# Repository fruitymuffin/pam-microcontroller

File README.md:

# pam-microcontroller
The AVR controller is based on the AVR64DA32 chip which is programmed via the UPDI interface.

## 1. Compiling
The C/C++ code is compiled using avr-gcc/avr-g++ and makes use of avr-libc. [Microchip Studio](https://www.microchip.com/en-us/tools-resources/develop/microchip-studio) was used as the IDE as it integrates the avr-g++ toolchain so building is easy.

## 2. Uploading
The serialUPDI interface was used to upload .hex or .elf files to the chip with the help of [avrdude](https://github.com/avrdudes/avrdude). An avrdude upload command can be added to Microchip Studio as a external tool to make uploading executables easier.
Go to Tools->External Tools and add a new tool. The tool was configured as:

Command:
```
C:\Program Files\avrdude-v7.3-windows-x64\avrdude.exe
```
Arguments:
```
-p avr64da32 -P COM5 -b 115200 -c serialupdi -C "C:\Program Files\avrdude-v7.3-windows-x64\avrdude.conf" -U flash:w:$(BinDir)\led-controller.hex:i
```

Initial Directory:
```
$(BinDir)
```

In order to set fuses with avrdude on the newer DA series chips, it was necessary to manually write it. Luckily the corrent fuse locations are specified in avrdude.conf under the DX family information. To enable the reset pin, the fuse was written by:
```
avrdude -c serialupdi -p avr64da32 -P com5 -U syscfg0:w:0xC8:m
```

## 3. Serial communication
The avr controller has a FTDI 230XS usb to serial chip. Which will typically show up as /dev/ttyUSBn on linux. To write to the port, we can open it as a file using fopen, however to do so we need to know which tty port our device is on. The device is not guaranteed to always be /dev/ttyUSB0.
To be able to access it consistently we can create a symlink to a known filename by creating a udev rule.

Create a file caled "N-my-rule.rules" in ```/etc/udev/rules.d/``` with the contents:
```
SUBSYSTEM=="tty", ATTRS{idVendor}=="0403", ATTRS{idProduct}=="6015", ATTRS{serial}=="DU0D13LG", SYMLINK+="ttypam-serial"
```

This creates a symlink called ```ttypam-serial``` to the tty port which matches the properties given (idVendor, idProduct, serial), so that we can now use ```/dev/ttypam-serial``` to access our device.

To get the required USB device info use:
```
udevadm info -a -n /dev/ttyUSB0 | grep '{serial}\|{idProduct}\|{idVendor}' | head -n3
```
Where ttyUSB0 is replaced with the tty port of the device. See ```lsusb```.

It might also be necessary to add the user to the dialout group to get permissions to usb devices.

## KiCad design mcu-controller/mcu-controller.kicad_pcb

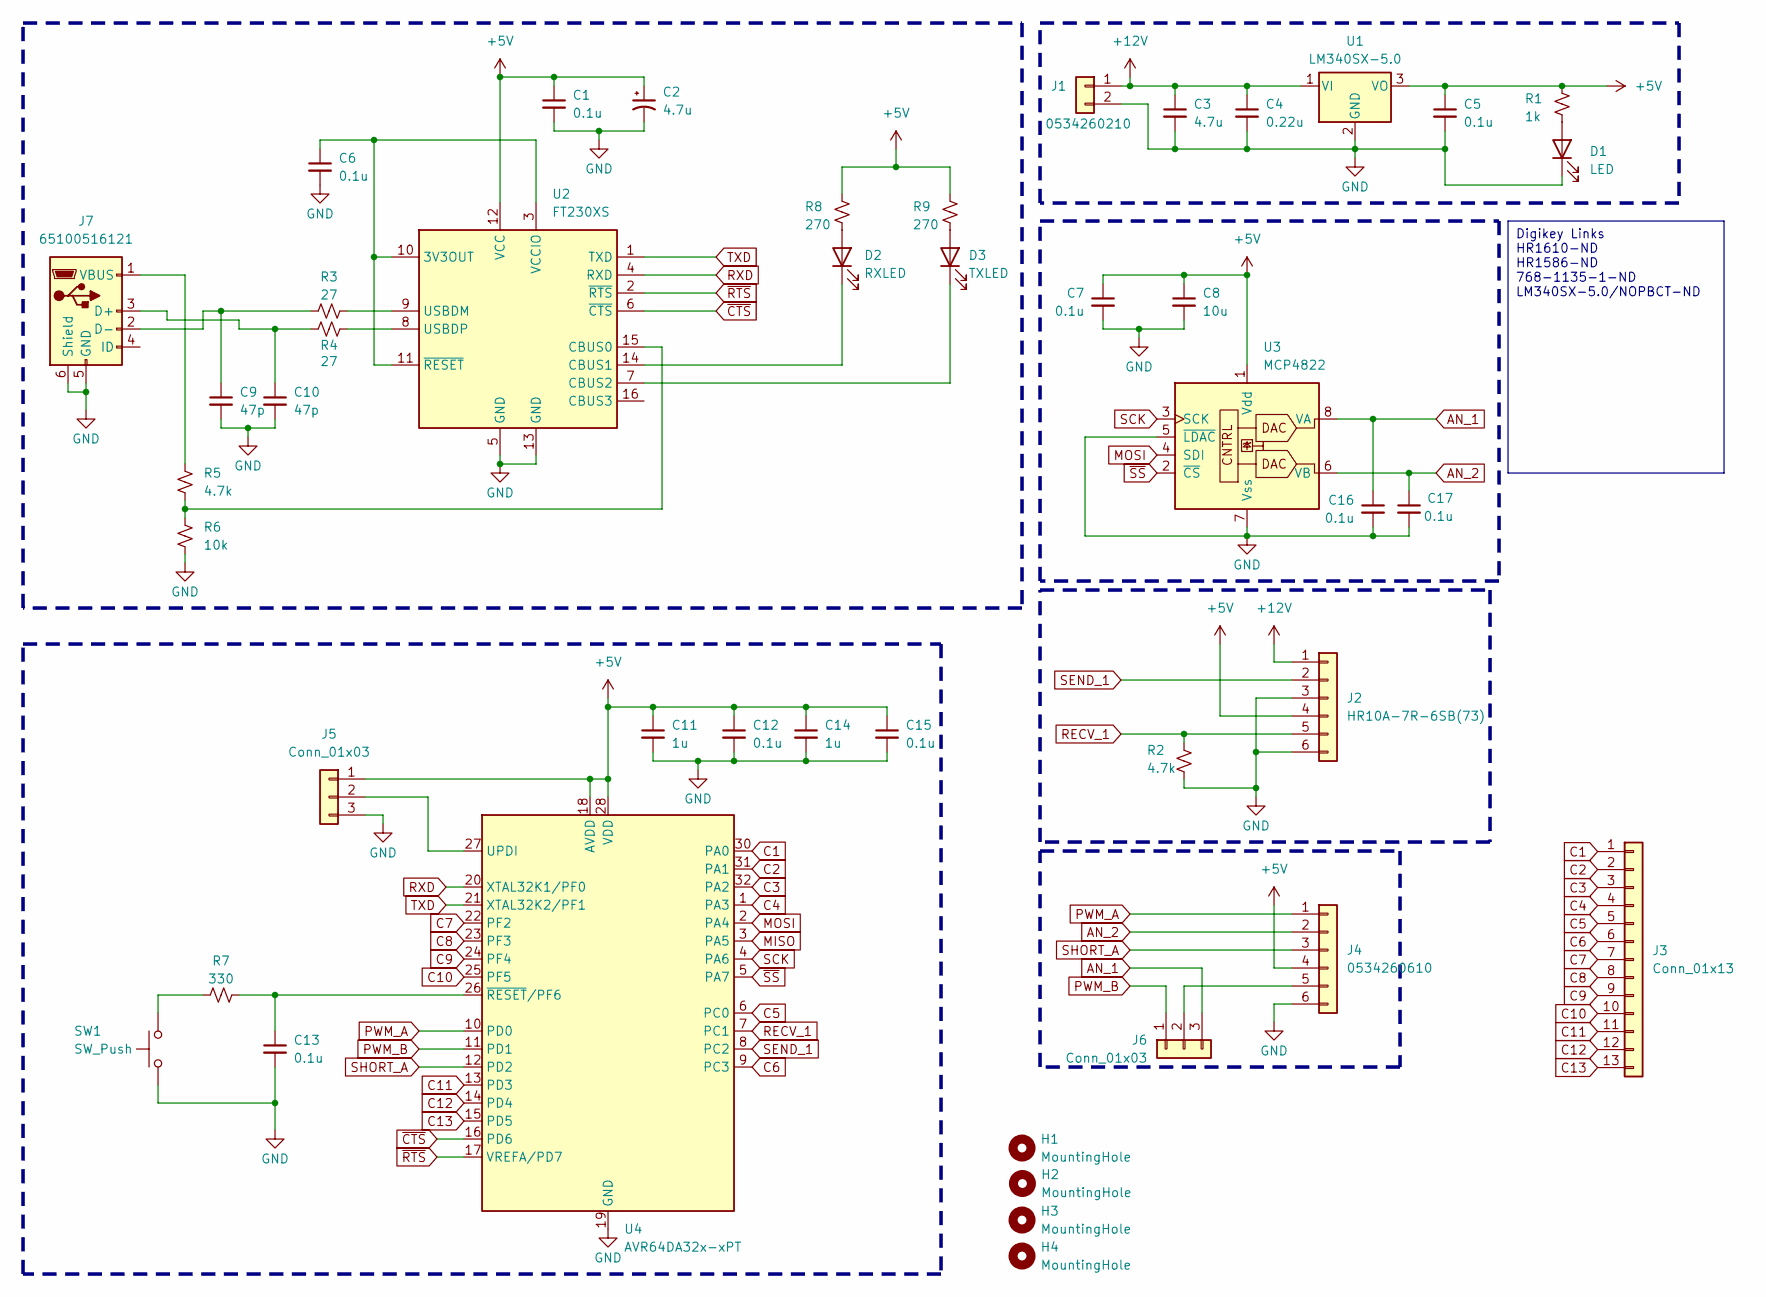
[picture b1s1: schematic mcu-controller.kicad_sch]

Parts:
C1, C5, C6, C7, C12, C13, C15, C16, C17: 0.1u; C_0805_2012Metric
C2, C3: 4.7u; C_0805_2012Metric
C4: 0.22u; C_0805_2012Metric
C8: 10u; C_1206_3216Metric
C9, C10: 47p; C_0805_2012Metric
C11, C14: 1u; C_0805_2012Metric
D1: LED; LED_0805_2012Metric
D2: RXLED; LED_0805_2012Metric
D3: TXLED; LED_0805_2012Metric
H1, H2, H3, H4: MountingHole; MountingHole_3.2mm_M3
J1: 0534260210; CON_534260210_MOL
J2: HR10A-7R-6SB(73)
J3: Conn_01x13; PinHeader_1x13_P2.54mm_Vertical
J4: 0534260610; CON_534260610_MOL
J5, J6: Conn_01x03; PinHeader_1x03_P2.54mm_Vertical
J7: 65100516121; USB_Mini-B_Wuerth_65100516121_Horizontal
R1: 1k; R_0805_2012Metric
R2, R5: 4.7k; R_0805_2012Metric
R3, R4: 27; R_0805_2012Metric
R6: 10k; R_0805_2012Metric
R7: 330; R_0805_2012Metric
R8, R9: 270; R_0805_2012Metric
SW1: SW_Push; SW_SPST_FSMSM
U1: LM340SX-5.0; TO-263-3_TabPin2
U2: FT230XS; SSOP-16_3.9x4.9mm_P0.635mm
U3: MCP4822; SOIC-8_3.9x4.9mm_P1.27mm
U4: AVR64DA32x-xPT; TQFP-32_7x7mm_P0.8mm

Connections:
+5V: C1.1, C2.1, C5.1, C7.1, C8.1, C11.1, C12.1, C14.1, C15.1, J2.4, J4.4, J5.1, R1.1, R8.1, R9.1, U1.3 (VO), U2.12 (VCC), U3.1 (Vdd), U4.18 (AVDD), U4.28 (VDD)
+12V: C3.1, C4.1, J1.1, J2.1, U1.1 (VI)
AN_1: C16.1, J6.3, U3.8 (VA)
AN_2: C17.1, J4.2, U3.6 (VB)
C1: J3.1, U4.30 (PA0)
C2: J3.2, U4.31 (PA1)
C3: J3.3, U4.32 (PA2)
C4: J3.4, U4.1 (PA3)
C5: J3.5, U4.6 (PC0)
C6: J3.6, U4.9 (PC3)
C7: J3.7, U4.22 (PF2)
C8: J3.8, U4.23 (PF3)
C9: J3.9, U4.24 (PF4)
C10: J3.10, U4.25 (PF5)
C11: J3.11, U4.13 (PD3)
C12: J3.12, U4.14 (PD4)
C13: J3.13, U4.15 (PD5)
GND: C1.2, C2.2, C3.2, C4.2, C5.2, C6.2, C7.2, C8.2, C9.2, C10.2, C11.2, C12.2, C13.2, C14.2, C15.2, C16.2, C17.2, D1.1 (K), J1.2, J2.3, J2.6, J4.6, J5.3, J7.5 (GND), J7.6 (Shield), R2.2, R6.2, SW1.1, U1.2 (GND), U2.5 (GND), U2.13 (GND), U3.5 (~LDAC), U3.7 (Vss), U4.19 (GND), U4.29 (GND)
MISO: U4.3 (PA5)
MOSI: U3.4 (SDI), U4.2 (PA4)
unnamed: D1.2 (A), R1.2
unnamed: D2.2 (A), R8.2
unnamed: D2.1 (K), U2.14 (CBUS1)
unnamed: D3.2 (A), R9.2
unnamed: D3.1 (K), U2.7 (CBUS2)
unnamed: J4.5, J6.2
unnamed: J5.2, U4.27 (UPDI)
unnamed: C10.1, J7.3 (D+), R4.1
unnamed: C9.1, J7.2 (D-), R3.1
unnamed: J7.1 (VBUS), R5.1
unnamed: R7.1, SW1.2
unnamed: C6.1, U2.3 (VCCIO), U2.10 (3V3OUT), U2.11 (~RESET)
unnamed: R5.2, R6.1, U2.15 (CBUS0)
unnamed: R3.2, U2.9 (USBDM)
unnamed: R4.2, U2.8 (USBDP)
unnamed: C13.1, R7.2, U4.26 (~RESET/PF6)
PWM_A: J4.1, U4.10 (PD0)
PWM_B: J6.1, U4.11 (PD1)
RECV_1: J2.5, R2.1, U4.7 (PC1)
RXD: U2.4 (RXD), U4.20 (XTAL32K1/PF0)
SCK: U3.3 (SCK), U4.4 (PA6)
SEND_1: J2.2, U4.8 (PC2)
SHORT_A: J4.3, U4.12 (PD2)
TXD: U2.1 (TXD), U4.21 (XTAL32K2/PF1)
~CTS: U2.6 (~CTS), U4.16 (PD6)
~RTS: U2.2 (~RTS), U4.17 (VREFA/PD7)
~SS: U3.2 (~CS), U4.5 (PA7)

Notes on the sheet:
Digikey Links HR1610-ND HR1586-ND 768-1135-1-ND LM340SX-5.0/NOPBCT-ND

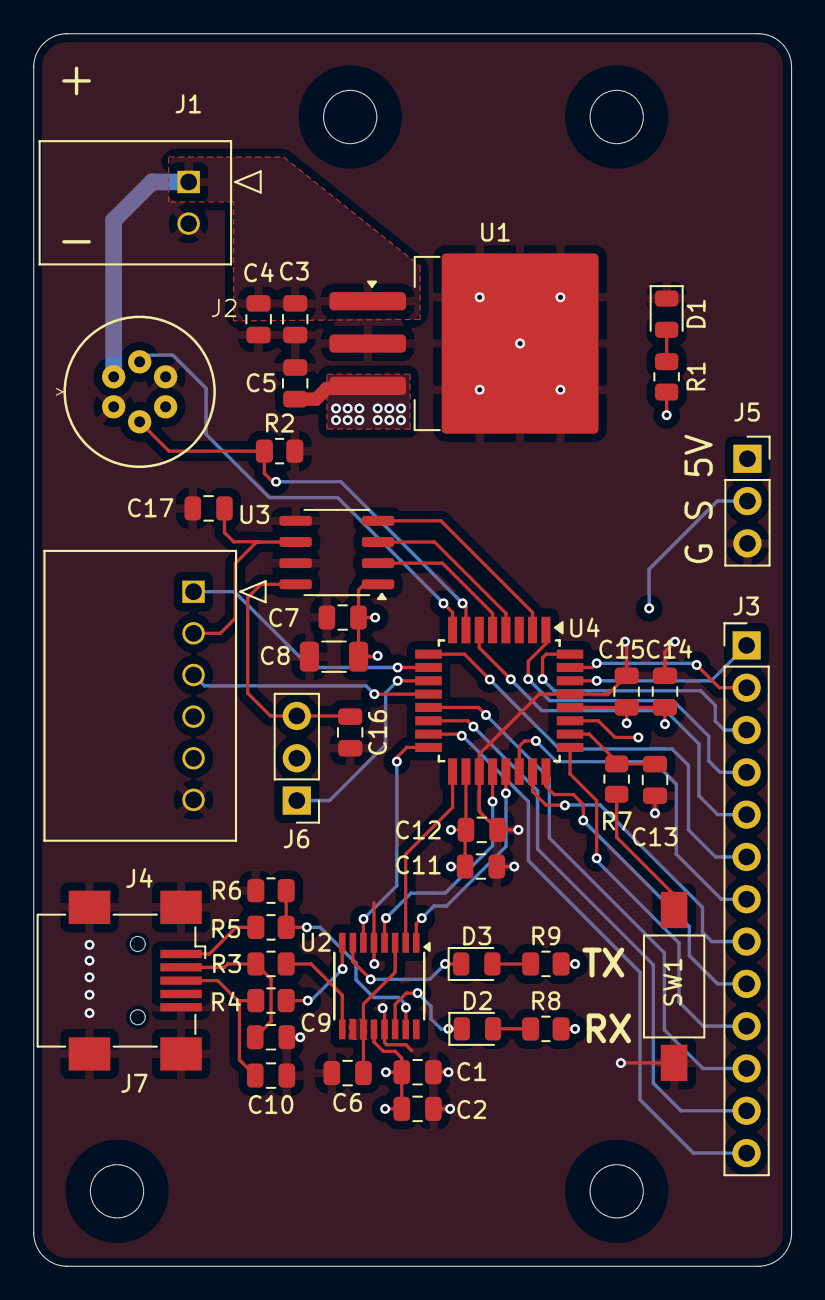
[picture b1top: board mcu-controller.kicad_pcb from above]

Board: 4 copper layers, 45.5 x 74.0 mm, 45 parts (0 on the bottom side), 46 nets.

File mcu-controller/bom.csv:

"Reference","Value","Datasheet","Footprint","Qty","DNP"
"C1,C5,C6,C7,C12,C13,C15,C16,C17","0.1u","~","Capacitor_SMD:C_0805_2012Metric","9",""
"C2,C3","4.7u","~","Capacitor_SMD:C_0805_2012Metric","2",""
"C4","0.22u","~","Capacitor_SMD:C_0805_2012Metric","1",""
"C8","10u","~","Capacitor_SMD:C_1206_3216Metric","1",""
"C9,C10","47p","Tantalum","Capacitor_SMD:C_0805_2012Metric","2",""
"C11,C14","1u","~","Capacitor_SMD:C_0805_2012Metric","2",""
"D1","LED","~","LED_SMD:LED_0805_2012Metric","1",""
"D2","RXLED","~","LED_SMD:LED_0805_2012Metric","1",""
"D3","TXLED","~","LED_SMD:LED_0805_2012Metric","1",""
"J1","0534260210","~","Library:CON_534260210_MOL","1",""
"J2","HR10A-7R-6SB(73)","~","Library:HR10A-7R-6SB(73)","1",""
"J3","Conn_01x13","~","Connector_PinHeader_2.54mm:PinHeader_1x13_P2.54mm_Vertical","1",""
"J4","0534260610","~","Library:CON_534260610_MOL","1",""
"J5,J6","Conn_01x03","~","Connector_PinHeader_2.54mm:PinHeader_1x03_P2.54mm_Vertical","2",""
"J7","65100516121","~","Connector_USB:USB_Mini-B_Wuerth_65100516121_Horizontal","1",""
"R1","1k","~","Resistor_SMD:R_0805_2012Metric","1",""
"R2,R5","4.7k","~","Resistor_SMD:R_0805_2012Metric","2",""
"R3,R4","27","~","Resistor_SMD:R_0805_2012Metric","2",""
"R6","10k","~","Resistor_SMD:R_0805_2012Metric","1",""
"R7","330","~","Resistor_SMD:R_0805_2012Metric","1",""
"R8,R9","270","~","Resistor_SMD:R_0805_2012Metric","2",""
"SW1","SW_Push","~","Button_Switch_SMD:SW_SPST_FSMSM","1",""
"U1","LM340SX-5.0","https://www.analog.com/media/en/technical-documentation/data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","Package_TO_SOT_SMD:TO-263-3_TabPin2","1",""
"U2","FT230XS","https://www.ftdichip.com/Support/Documents/DataSheets/ICs/DS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","Package_SO:SSOP-16_3.9x4.9mm_P0.635mm","1",""
"U3","MCP4822","http://ww1.microchip.com/downloads/en/DeviceDoc/20002249B.pdf","Package_SO:SOIC-8_3.9x4.9mm_P1.27mm","1",""
"U4","AVR64DA32x-xPT","https://ww1.microchip.com/downloads/en/DeviceDoc/AVR64DA28-3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","Package_QFP:TQFP-32_7x7mm_P0.8mm","1",""

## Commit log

2024-05-07 New repo, moved files from pam repo
2024-05-07 Removed junk files
